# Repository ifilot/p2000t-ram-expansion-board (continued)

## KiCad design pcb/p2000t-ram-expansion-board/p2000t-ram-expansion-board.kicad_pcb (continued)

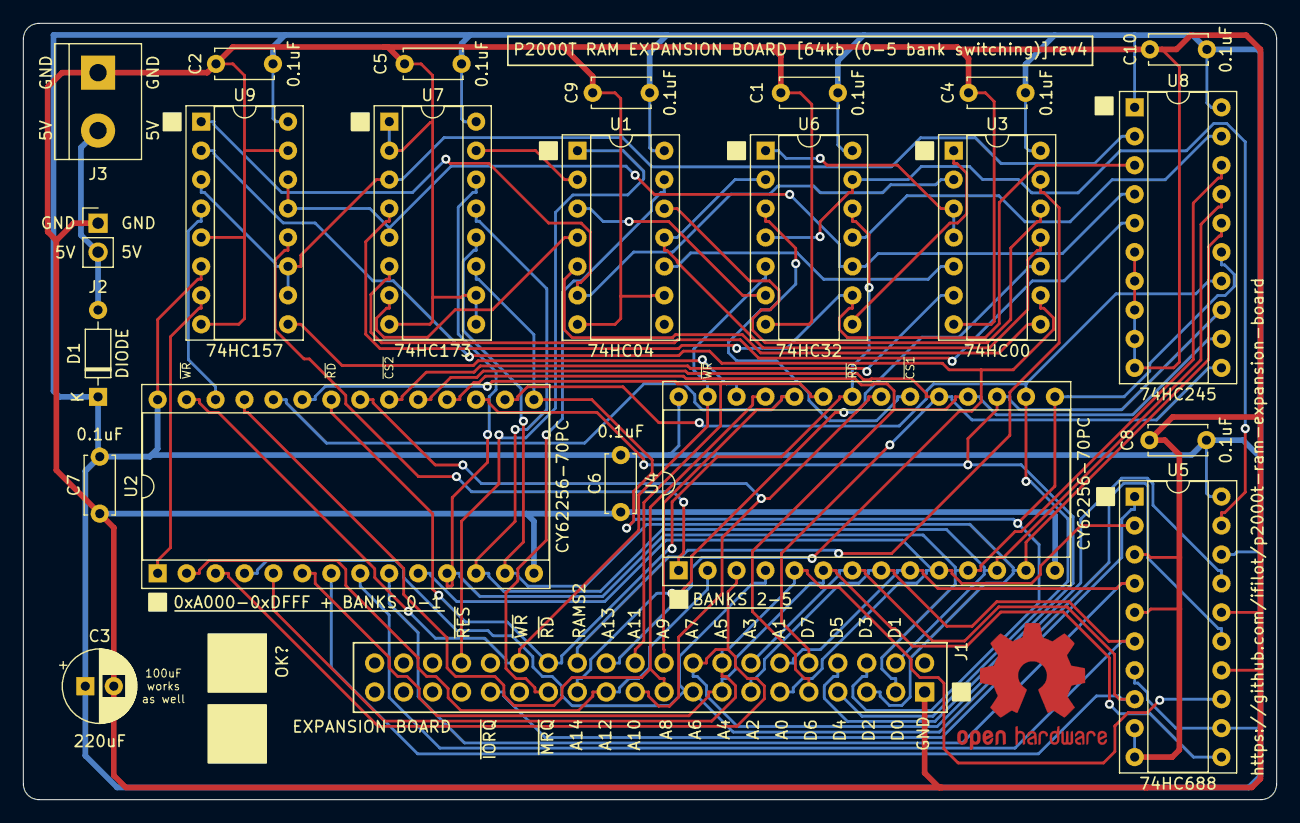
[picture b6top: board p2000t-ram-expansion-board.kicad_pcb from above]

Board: 2 copper layers, 110.0 x 68.1 mm, 24 parts (1 on the bottom side), 54 nets.

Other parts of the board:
LOGO1: OSHW-Logo2_14.6x12mm_Copper_AND_Mask

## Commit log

2023-10-18 Adding logism circuit
2023-10-21 Revising design
2023-10-22 Adding reverse polarity diode and silk screen comments
2023-10-23 Improving layout
2023-10-24 Adding GERBERS
2023-10-31 Adding ramtest script
2023-11-02 Revising PCB and updating code
2023-11-03 Polishing PCB
2023-11-10 Refactoring ramtester utility
2023-11-10 Fixing banks
2023-11-11 Expanding ram tester software
2023-11-12 Adding README.md, images and CI/CD
2023-11-12 Expanding README and polishing CI/CD
2023-11-12 Updating SVG
2023-11-12 Putting link to Github repo on PCB
2023-11-12 Expanding README.md
2023-11-16 Adding 74HC245
2023-11-24 Fixing connection
2023-11-25 Revising board and fixing bugs
2023-11-25 Updating README.md
2023-11-25 Updating schematic
2023-12-23 Replacing images
2023-12-23 Board revision 3 (#2)
    * Adding 74HC245
    * Fixing connection
    * Revising board and fixing bugs
    * Updating README.md
    * Updating schematic
    * Replacing images
2023-12-26 Expanding testsuite and adding comments
2023-12-26 Adding ramtester image
2023-12-26 Expanding memory testing module (#3)
    * Expanding testsuite and adding comments
    * Adding ramtester image
2023-12-30 Update README.md (#4)
2024-01-06 Small fixes in schematic
2024-01-06 Adding SMD version of P2000T expansion board
2024-01-08 Storing before routing
2024-01-13 Adding gerbers and SVG
2024-01-18 Adding support for 1056kb RAM expansion board to ramtester
2024-01-18 Adding pictures of 1056kb expansion board
2024-01-19 Adding SVG file
2024-01-20 Replacing pictures
2024-03-28 Version 1056kb (#5)
    * Initial commit
    * Storing before routing
    * Adding gerbers and SVG
    * Adding support for 1056kb RAM expansion board to ramtester
    * Adding pictures of 1056kb expansion board
    * Adding SVG file
2024-04-26 Initial commit RAM tester rewrite
2024-04-28 Revising ramtester
2024-04-28 Small bugfixes
2024-05-03 Expansion RAM test
2024-05-03 Tweaking tests
2024-05-03 Fixing bug in wiring
2024-05-03 Fixing another bug 74HC74
2024-05-03 Changing size
2024-05-12 Revising image
2024-05-20 Fixing small bugs in ramtest
2024-05-20 Revising PCBs
2024-05-20 Version 2080kb (#6)
    * Initial commit
    * Adding gerbers
    * Fixing bug in wiring
    * Fixing another bug 74HC74
    * Changing size
    * Revising PCBs
2024-06-02 Revision of RAM testing utility (#7)
    * Initial commit RAM tester rewrite
    * Revising ramtester
    * Small bugfixes
    * Expansion RAM test
    * Tweaking tests
    * Fixing small bugs in ramtest
2024-06-02 Fixing bug in GA
2024-06-02 Increasing compilation depth
2024-06-02 Showing compilation output
2024-06-02 Auto-renaming
2024-08-06 Adding 128KiB SMD design
2024-08-07 Changing silk screen
2024-08-07 Saving schematic
2024-08-18 Expanding README and ram testing routines
2024-08-18 Revising board layout
2024-08-31 Adding images
2024-08-31 Creating 128 KiB memory expansion using SMD components (#8)
    * Adding 128KiB SMD design
    * Changing silk screen
    * Saving schematic
    * Expanding README and ram testing routines
    * Revising board layout
    * Adding images
2025-03-29 Initial commit CPLD version of RAM expansion board
2025-03-29 Initial commit CPLD-based RAM expansion
2025-04-05 Fixing CUPL script
2025-04-05 Further revising README.md
2025-04-05 Reintroducing picture
2025-04-05 Fixing artifact level
2025-04-05 CPLD version of the 128 KiB memory expansion board (#9)
    * Initial commit CPLD version of RAM expansion board
    * Initial commit CPLD-based RAM expansion
    * Fixing CUPL script
    * Expanding README.md
    * Further revising README.md
    * Reintroducing picture
2025-06-21 Initial commit new board design
2025-06-21 Expanding to 4 RAM chips
2025-06-22 Finalizing prototype
2025-07-14 Adjusting CUPL
2025-08-09 Fixing CUPL code for multi-ram
2025-08-09 Expanding test suite
2025-08-10 Further tuning ram tester
2025-08-12 Implementing bank counting routine in RAM tester
2025-08-12 Adding comments
2025-08-12 Final tweaks to RAM tester
2025-08-12 New 512 KiB SMD-CPLD board (#10)
    * Finalizing prototype
    * Adjusting CUPL
    * Fixing CUPL code for multi-ram
    * Expanding test suite
    * Further tuning ram tester
    * Implementing bank counting routine in RAM tester
